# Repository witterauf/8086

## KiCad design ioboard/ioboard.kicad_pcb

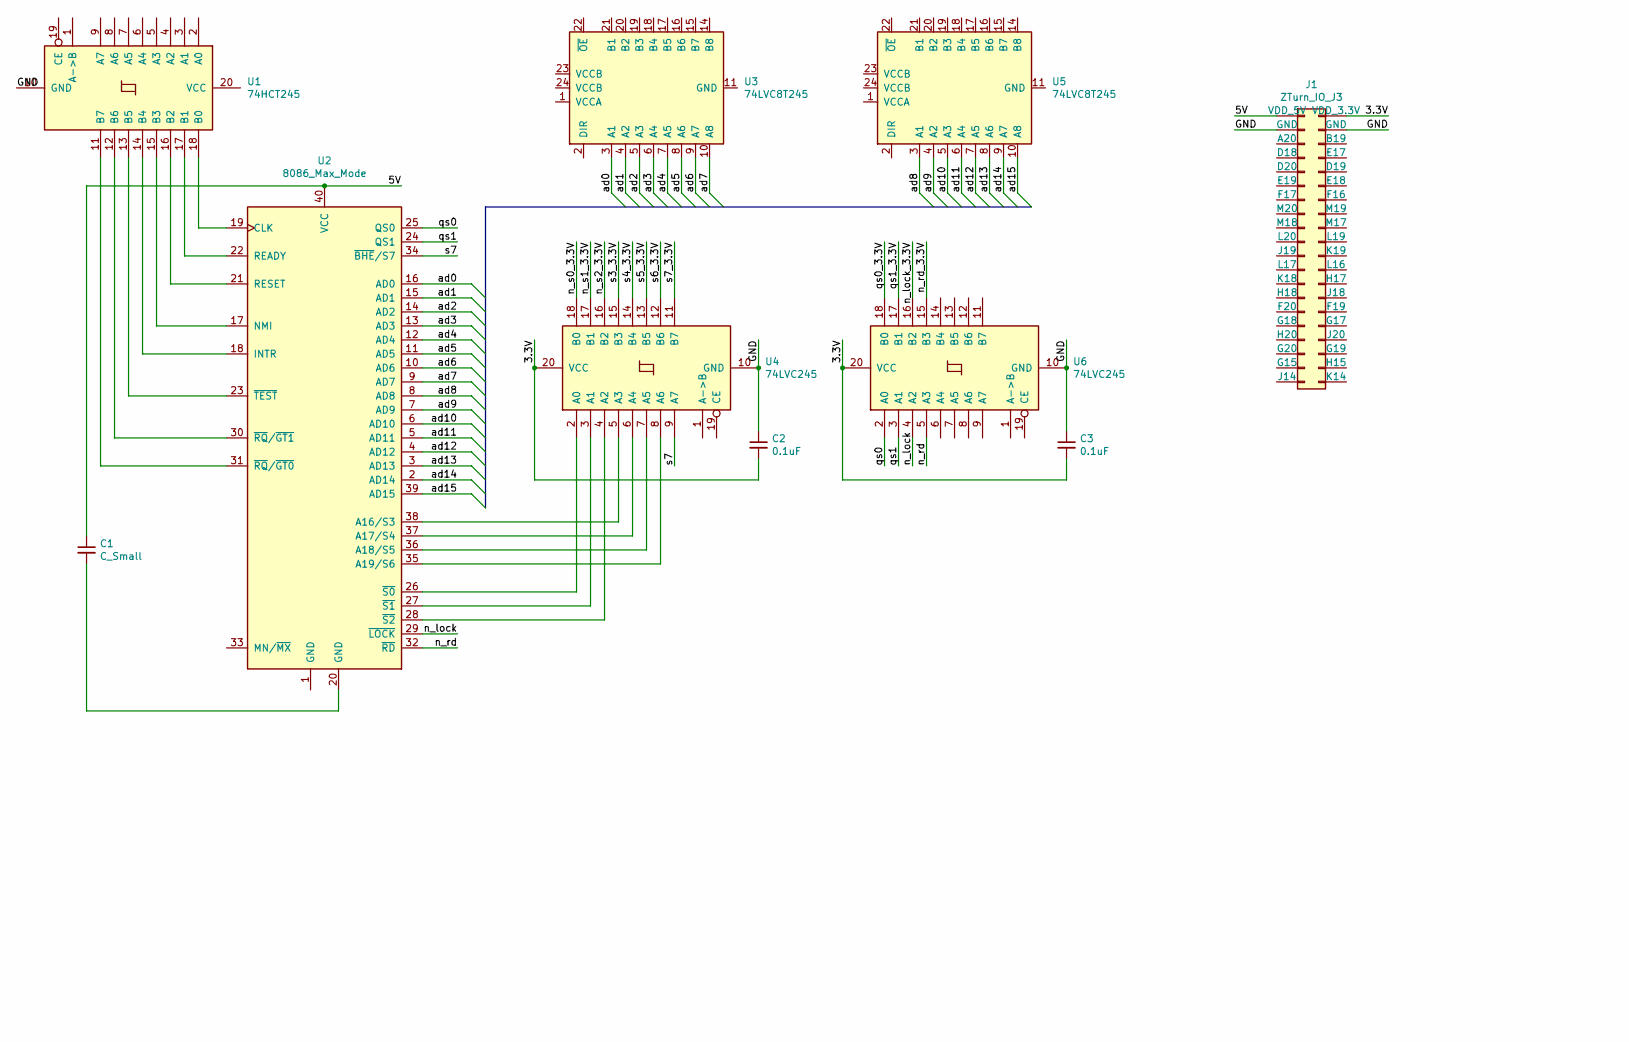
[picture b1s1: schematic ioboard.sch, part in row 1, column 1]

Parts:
C1: C_Small; C_Disc_D3.0mm_W1.6mm_P2.50mm
C2, C3: 0.1uF; C_Disc_D3.0mm_W1.6mm_P2.50mm
J1: ZTurn_IO_J3; PinHeader_2x20_P2.54mm_Vertical
U1: 74HCT245; DIP-20_W7.62mm
U2: 8086_Max_Mode; DIP-40_W15.24mm
U3, U5: 74LVC8T245; DIP-24_W15.24mm
U4, U6: 74LVC245; DIP-20_W7.62mm

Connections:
/3.3V: C2.2, C3.2, J1.2 (VDD_3.3V), U4.20 (VCC), U6.20 (VCC)
/5V: C1.1, J1.1 (VDD_5V), U2.40 (VCC)
/GND: C2.1, C3.1, J1.3 (GND), J1.4 (GND), U1.10 (GND), U4.10 (GND), U6.10 (GND)
/ad0: U2.16 (AD0), U3.3 (A1)
/ad1: U2.15 (AD1), U3.4 (A2)
/ad2: U2.14 (AD2), U3.5 (A3)
/ad3: U2.13 (AD3), U3.6 (A4)
/ad4: U2.12 (AD4), U3.7 (A5)
/ad5: U2.11 (AD5), U3.8 (A6)
/ad6: U2.10 (AD6), U3.9 (A7)
/ad7: U2.9 (AD7), U3.10 (A8)
/ad8: U2.8 (AD8), U5.3 (A1)
/ad9: U2.7 (AD9), U5.4 (A2)
/ad10: U2.6 (AD10), U5.5 (A3)
/ad11: U2.5 (AD11), U5.6 (A4)
/ad12: U2.4 (AD12), U5.7 (A5)
/ad13: U2.3 (AD13), U5.8 (A6)
/ad14: U2.2 (AD14), U5.9 (A7)
/ad15: U2.39 (AD15), U5.10 (A8)
/n_lock: U2.29 (~LOCK~), U6.4 (A2)
/n_lock_3.3V: U6.16 (B2)
/n_rd: U2.32 (~RD~), U6.5 (A3)
/n_rd_3.3V: U6.15 (B3)
/n_s0_3.3V: U4.18 (B0)
/n_s1_3.3V: U4.17 (B1)
/n_s2_3.3V: U4.16 (B2)
/qs0: U2.25 (QS0), U6.2 (A0)
/qs0_3.3V: U6.18 (B0)
/qs1: U2.24 (QS1), U6.3 (A1)
/qs1_3.3V: U6.17 (B1)
/s3_3.3V: U4.15 (B3)
/s4_3.3V: U4.14 (B4)
/s5_3.3V: U4.13 (B5)
/s6_3.3V: U4.12 (B6)
/s7: U2.34 (~BHE~/S7), U4.9 (A7)
/s7_3.3V: U4.11 (B7)
unnamed: C1.2, U2.20 (GND)
unnamed: U1.11 (B7), U2.31 (~RQ~/~GT0~)
unnamed: U1.12 (B6), U2.30 (~RQ~/~GT1~)
unnamed: U1.13 (B5), U2.23 (~TEST~)
unnamed: U1.14 (B4), U2.18 (INTR)
unnamed: U1.15 (B3), U2.17 (NMI)
unnamed: U1.16 (B2), U2.21 (RESET)
unnamed: U1.17 (B1), U2.22 (READY)
unnamed: U1.18 (B0), U2.19 (CLK)
unnamed: U2.26 (~S0~), U4.2 (A0)
unnamed: U2.27 (~S1~), U4.3 (A1)
unnamed: U2.28 (~S2~), U4.4 (A2)
unnamed: U2.35 (A19/S6), U4.8 (A6)
unnamed: U2.36 (A18/S5), U4.7 (A5)
unnamed: U2.37 (A17/S4), U4.6 (A4)
unnamed: U2.38 (A16/S3), U4.5 (A3)
unnamed: U3.11 (GND), U3.12 (GND), U3.13 (GND)
unnamed: U5.11 (GND), U5.12 (GND), U5.13 (GND)

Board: 2 copper layers, 10 parts (0 on the bottom side), 42 nets, no tracks yet.

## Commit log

2020-10-30 Design Z-Turn IO Cape connector as component
2020-11-10 Add footprints and experiment with net lists
2020-11-15 Rework IO board design
